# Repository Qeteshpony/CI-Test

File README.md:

# CI-Test

[Hardware Documentation](https://qeteshpony.github.io/CI-Test)

Test project for CI changes

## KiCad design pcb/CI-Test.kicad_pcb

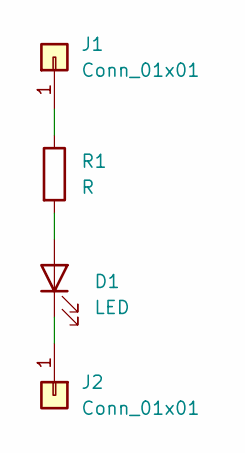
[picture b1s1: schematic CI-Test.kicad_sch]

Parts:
D1: LED; LED_D5.0mm
J1, J2: Conn_01x01; SolderWire-0.5sqmm_1x01_D0.9mm_OD2.1mm
R1: R; R_Axial_DIN0207_L6.3mm_D2.5mm_P7.62mm_Horizontal

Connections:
unnamed: D1.2 (A), R1.2
unnamed: D1.1 (K), J2.1
unnamed: J1.1, R1.1

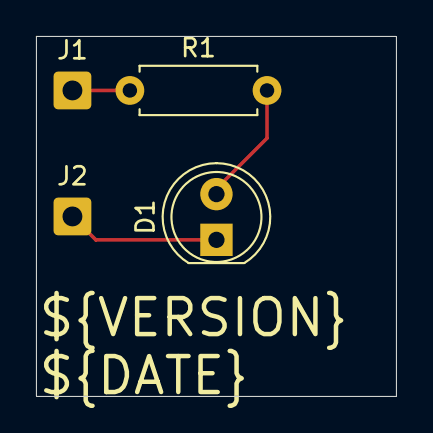
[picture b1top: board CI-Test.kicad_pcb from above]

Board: 2 copper layers, 20.0 x 20.0 mm, 4 parts (0 on the bottom side), 3 nets.

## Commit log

2024-08-18 feat: initial commit
2024-08-18 fix: testfix
2024-08-18 chore(main): release 1.0.0
2024-08-18 fix: another test
2024-08-18 chore(main): release 1.0.1
2024-08-18 fix: aaand another one
2024-08-18 chore(main): release 1.0.2
2024-08-21 ci: remove dependency
2024-08-21 chore(main): release 1.0.3
2024-10-11 ci: replace obsolete functions
2024-10-11 feat: bla
2024-10-11 ci: fix zip options
2024-10-11 chore(main): release 1.1.0
